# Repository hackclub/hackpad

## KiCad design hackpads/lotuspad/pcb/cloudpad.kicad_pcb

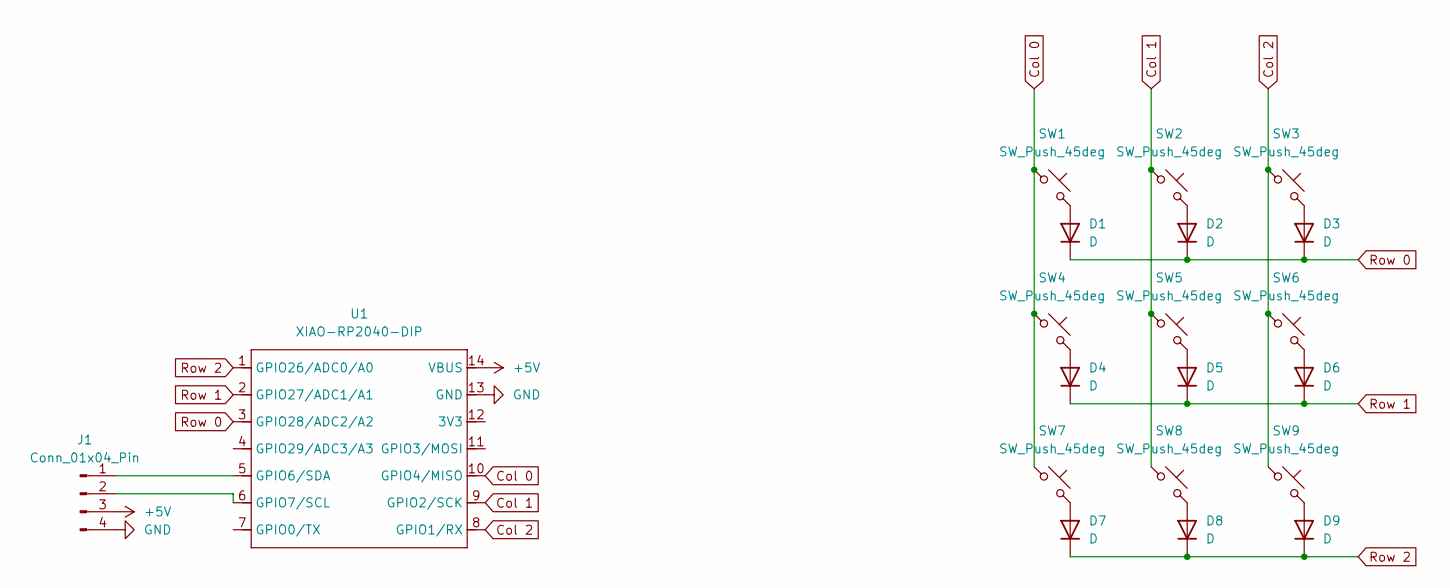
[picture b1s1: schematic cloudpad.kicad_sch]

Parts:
D1, D2, D3, D4, D5, D6, D7, D8, D9: D; Diode_DO-35
J1: Conn_01x04_Pin; MODULE_DM-OLED096-636
SW1, SW2, SW3, SW4, SW5, SW6, SW7, SW8, SW9: SW_Push_45deg; SW_Cherry_MX_1.00u_PCB
U1: XIAO-RP2040-DIP

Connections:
+5V: J1.3, U1.14 (VBUS)
Col 0: SW1.1, SW4.1, SW7.1, U1.10 (GPIO4/MISO)
Col 1: SW2.1, SW5.1, SW8.1, U1.9 (GPIO2/SCK)
Col 2: SW3.1, SW6.1, SW9.1, U1.8 (GPIO1/RX)
GND: J1.4, U1.13 (GND)
unnamed: D1.2 (A), SW1.2
unnamed: D2.2 (A), SW2.2
unnamed: D3.2 (A), SW3.2
unnamed: D4.2 (A), SW4.2
unnamed: D5.2 (A), SW5.2
unnamed: D6.2 (A), SW6.2
unnamed: D7.2 (A), SW7.2
unnamed: D8.2 (A), SW8.2
unnamed: D9.2 (A), SW9.2
unnamed: J1.1, U1.5 (GPIO6/SDA)
unnamed: J1.2, U1.6 (GPIO7/SCL)
Row 0: D1.1 (K), D2.1 (K), D3.1 (K), U1.3 (GPIO28/ADC2/A2)
Row 1: D4.1 (K), D5.1 (K), D6.1 (K), U1.2 (GPIO27/ADC1/A1)
Row 2: D7.1 (K), D8.1 (K), D9.1 (K), U1.1 (GPIO26/ADC0/A0)

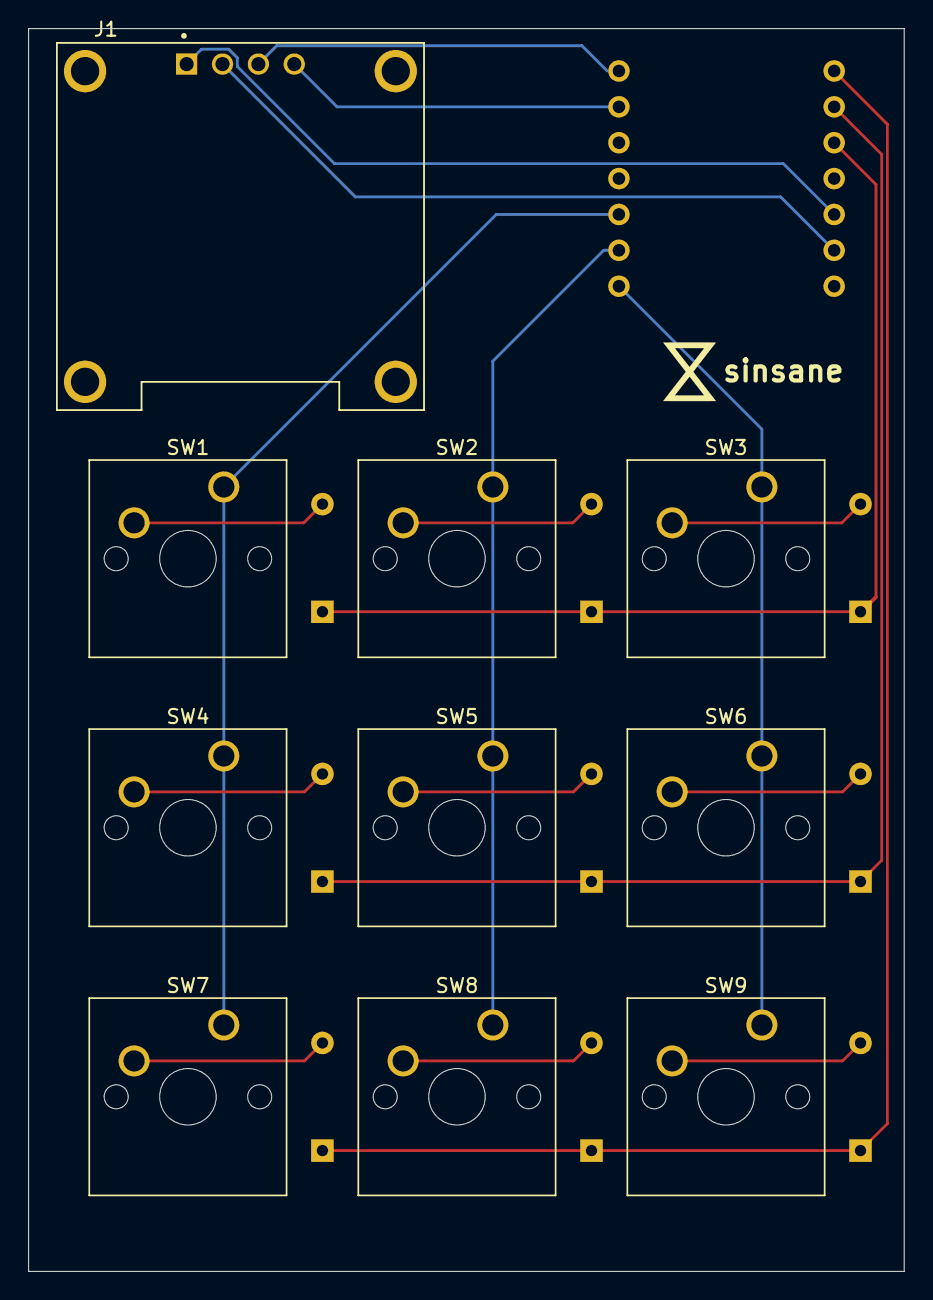
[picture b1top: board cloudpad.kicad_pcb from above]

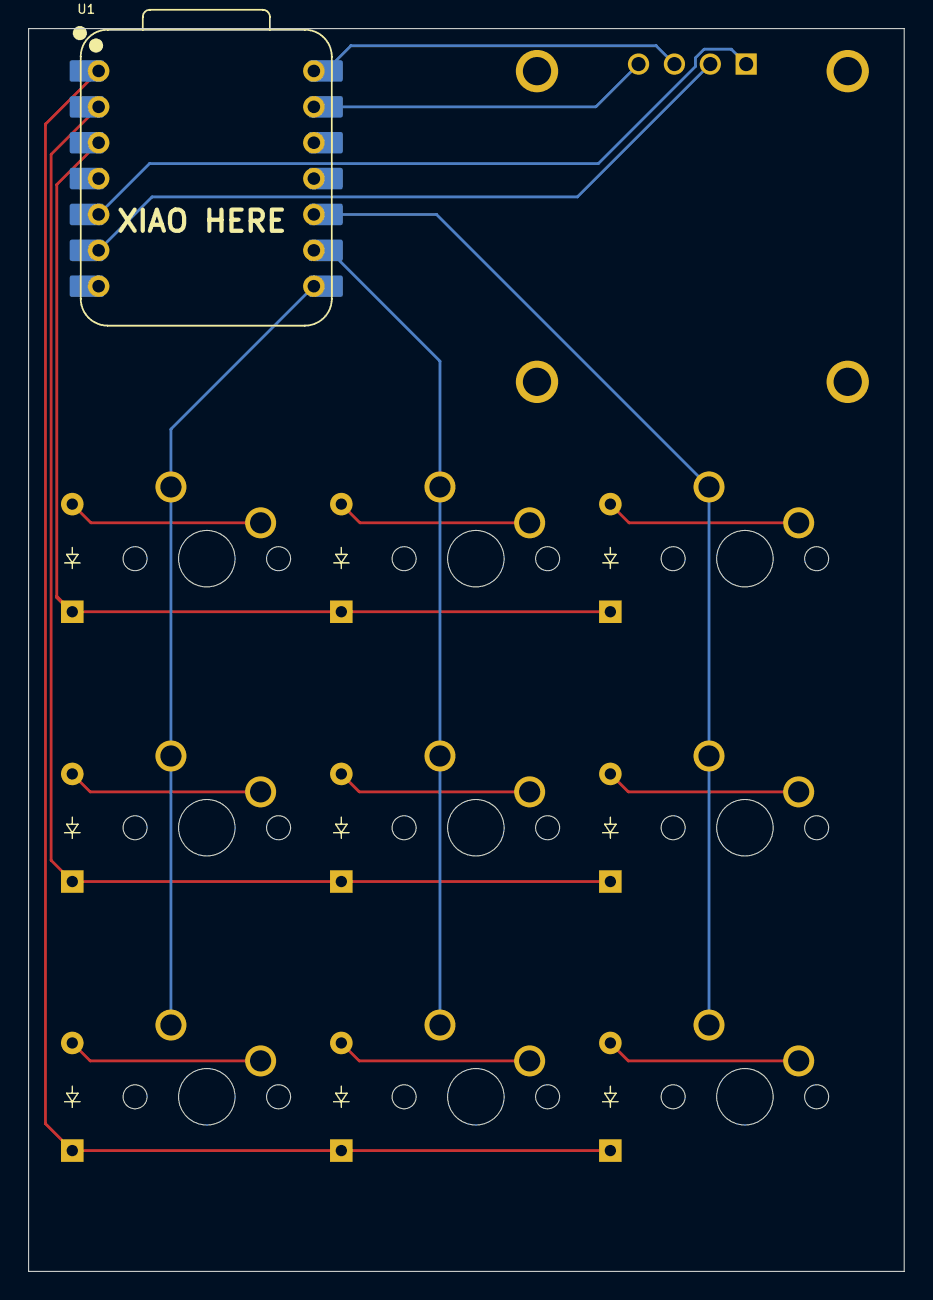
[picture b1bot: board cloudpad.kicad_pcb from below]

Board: 2 copper layers, 62.0 x 88.0 mm, 20 parts (10 on the bottom side), 19 nets.

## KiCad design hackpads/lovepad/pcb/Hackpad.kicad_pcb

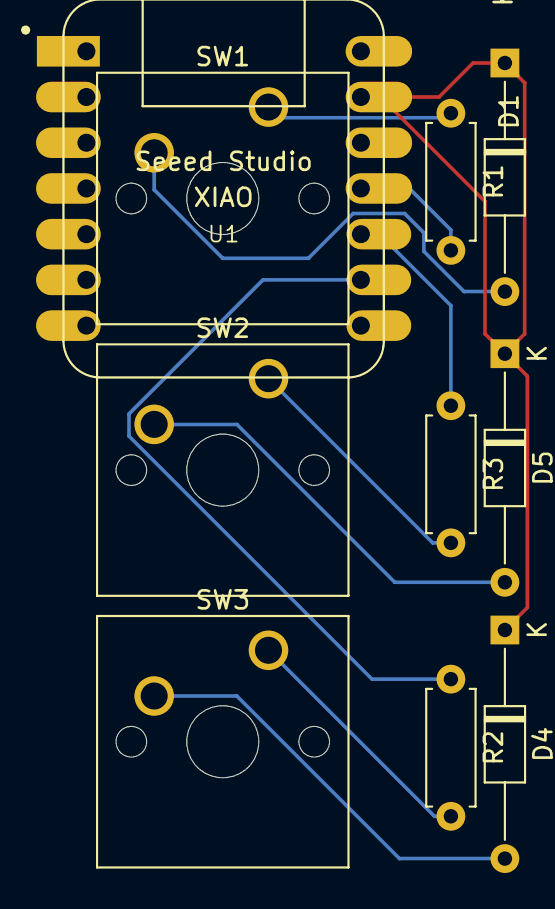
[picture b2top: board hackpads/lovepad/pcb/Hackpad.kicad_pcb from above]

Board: 2 copper layers, 10 parts (0 on the bottom side), 10 nets.

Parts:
D1, D4, D5: LED; D_DO-35_SOD27_P12.70mm_Horizontal
R1, R2, R3: R; R_Axial_DIN0207_L6.3mm_D2.5mm_P7.62mm_Horizontal
SW1, SW2, SW3: SW_Push; SW_Cherry_MX_1.00u_PCB
U1: Seeed Studio XIAO SAMD21; XIAO-Generic-Hybrid-14P-2.54-21X17.8MM

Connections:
GND: D1.1 (K), D4.1 (K), D5.1 (K), U1.13 (GND)
unnamed: D1.2 (A), SW1.2
unnamed: D4.2 (A), SW3.2
unnamed: D5.2 (A), SW2.2
unnamed: R1.1, SW1.1
unnamed: R2.2, SW3.1
unnamed: R3.2, SW2.1
unnamed: R3.1, U1.10 (PA5_A9_D9_MISO)
unnamed: R1.2, U1.11 (PA6_A10_D10_MOSI)
unnamed: R2.1, U1.9 (PA7_A8_D8_SCK)

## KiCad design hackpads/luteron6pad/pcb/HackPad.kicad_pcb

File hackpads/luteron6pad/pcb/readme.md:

The zip file is the gerber files for production.
The rest are KiCad project files.

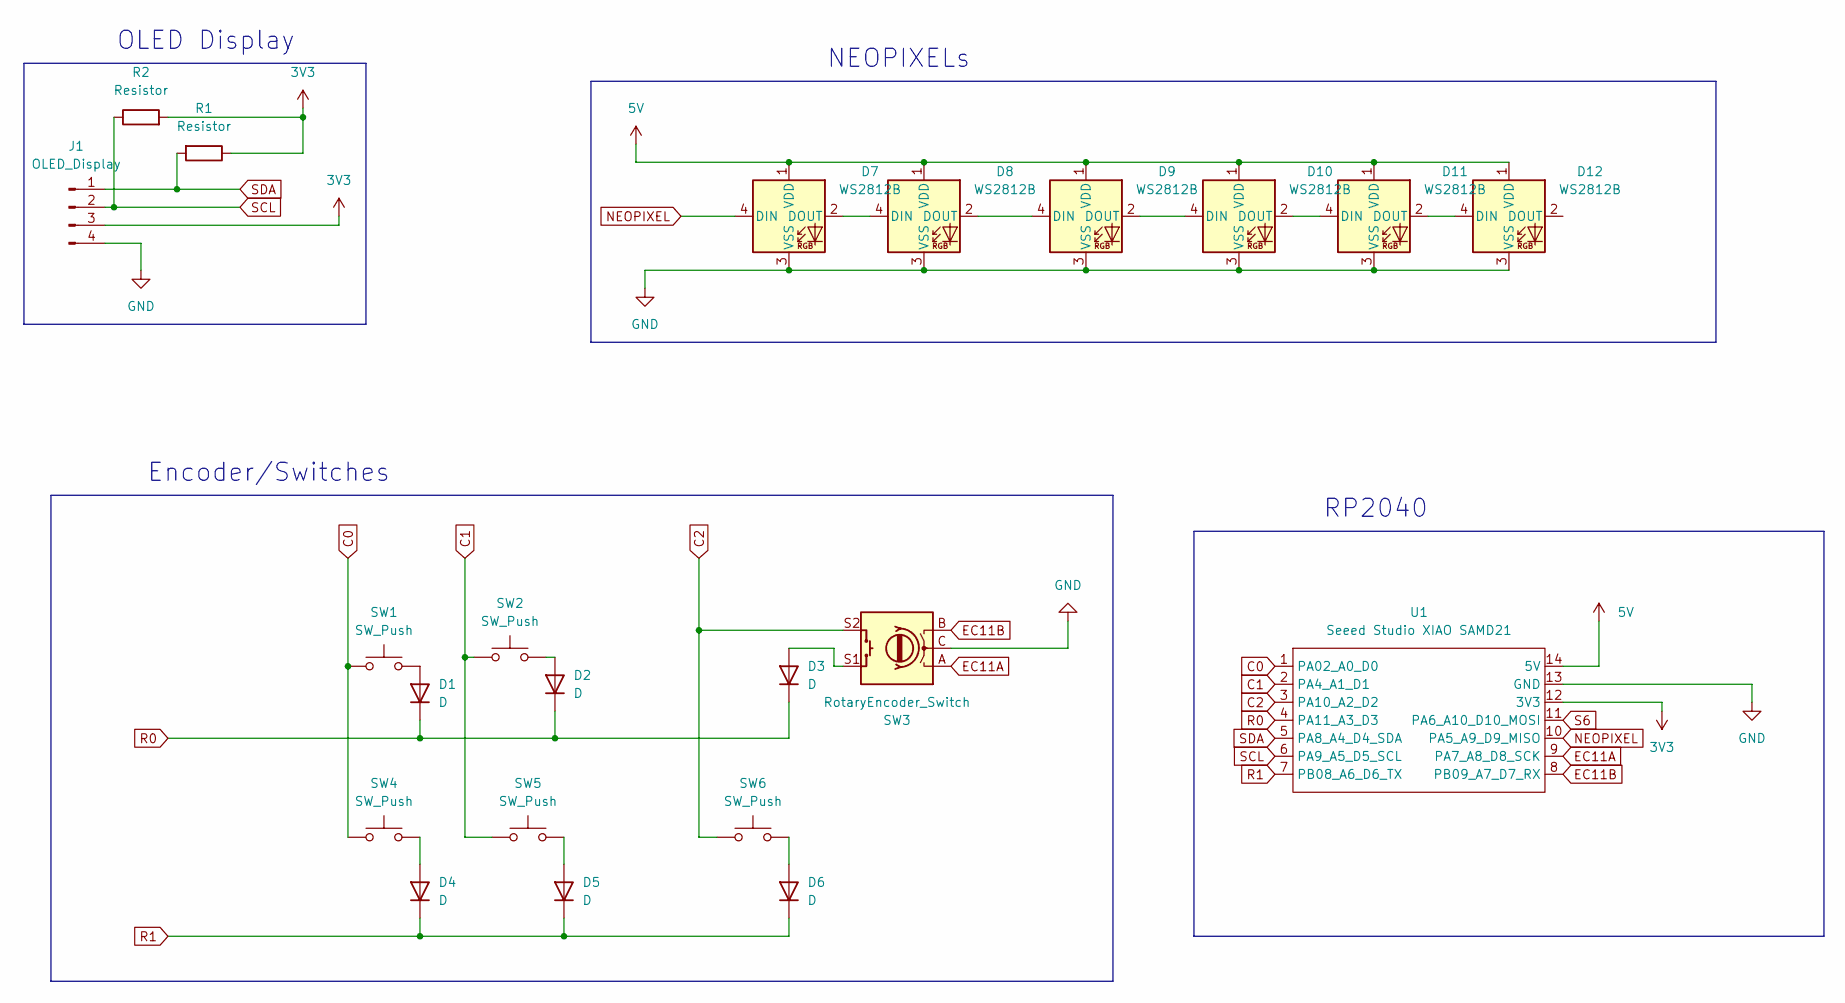
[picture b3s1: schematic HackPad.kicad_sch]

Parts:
D1, D2, D3, D4, D5, D6: D; D_DO-35_SOD27_P7.62mm_Horizontal
D7, D8, D9, D10, D11, D12: WS2812B; LED_WS2812B_PLCC4_5.0x5.0mm_P3.2mm
J1: OLED_Display; OLED_128x64
R1, R2: Resistor; R_0402_1005Metric
SW1, SW2, SW4, SW5, SW6: SW_Push; MX_PCB_1.00u
SW3: RotaryEncoder_Switch; Encoder_EC11_MX
U1: Seeed Studio XIAO SAMD21; Seeed_XIAO_RP2040

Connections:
3V3: J1.3, R1.1, R2.2, U1.12 (3V3)
5V: D7.1 (VDD), D8.1 (VDD), D9.1 (VDD), D10.1 (VDD), D11.1 (VDD), D12.1 (VDD), U1.14 (5V)
C0: SW1.1, SW4.1, U1.1 (PA02_A0_D0)
C1: SW2.1, SW5.1, U1.2 (PA4_A1_D1)
C2: SW3.S2, SW6.1, U1.3 (PA10_A2_D2)
EC11A: SW3.A, U1.9 (PA7_A8_D8_SCK)
EC11B: SW3.B, U1.8 (PB09_A7_D7_RX)
GND: D7.3 (VSS), D8.3 (VSS), D9.3 (VSS), D10.3 (VSS), D11.3 (VSS), D12.3 (VSS), J1.4, SW3.C, U1.13 (GND)
NEOPIXEL: D7.4 (DIN), U1.10 (PA5_A9_D9_MISO)
unnamed: D1.2 (A), SW1.2
unnamed: D2.2 (A), SW2.2
unnamed: D3.2 (A), SW3.S1
unnamed: D4.2 (A), SW4.2
unnamed: D5.2 (A), SW5.2
unnamed: D6.2 (A), SW6.2
unnamed: D7.2 (DOUT), D8.4 (DIN)
unnamed: D8.2 (DOUT), D9.4 (DIN)
unnamed: D9.2 (DOUT), D10.4 (DIN)
unnamed: D10.2 (DOUT), D11.4 (DIN)
unnamed: D11.2 (DOUT), D12.4 (DIN)
R0: D1.1 (K), D2.1 (K), D3.1 (K), U1.4 (PA11_A3_D3)
R1: D4.1 (K), D5.1 (K), D6.1 (K), U1.7 (PB08_A6_D6_TX)
S6: U1.11 (PA6_A10_D10_MOSI)
SCL: J1.2, R2.1, U1.6 (PA9_A5_D5_SCL)
SDA: J1.1, R1.2, U1.5 (PA8_A4_D4_SDA)

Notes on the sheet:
RP2040
OLED Display
NEOPIXELs
Encoder/Switches

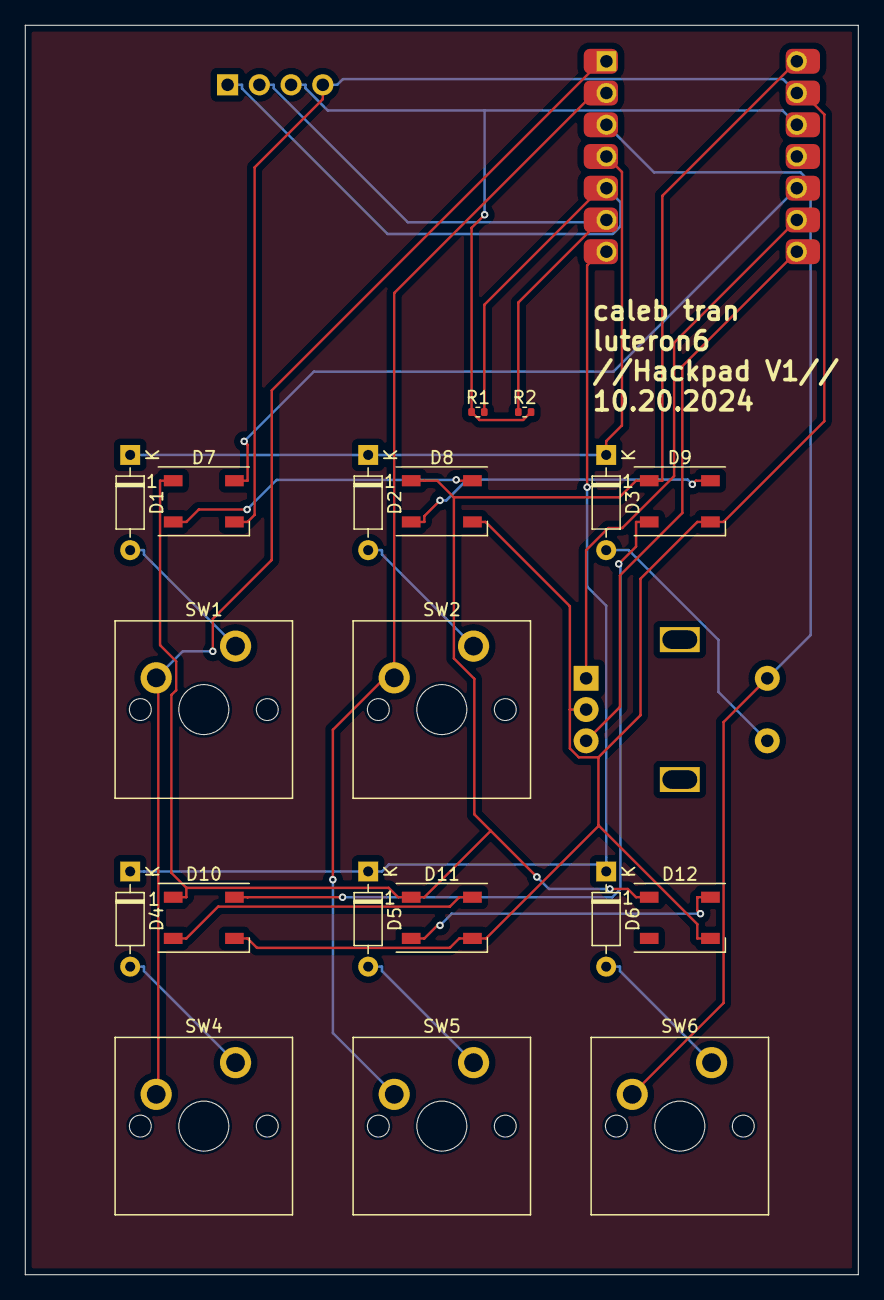
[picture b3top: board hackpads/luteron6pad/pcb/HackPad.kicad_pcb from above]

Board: 2 copper layers, 66.7 x 100.0 mm, 22 parts (0 on the bottom side), 24 nets.

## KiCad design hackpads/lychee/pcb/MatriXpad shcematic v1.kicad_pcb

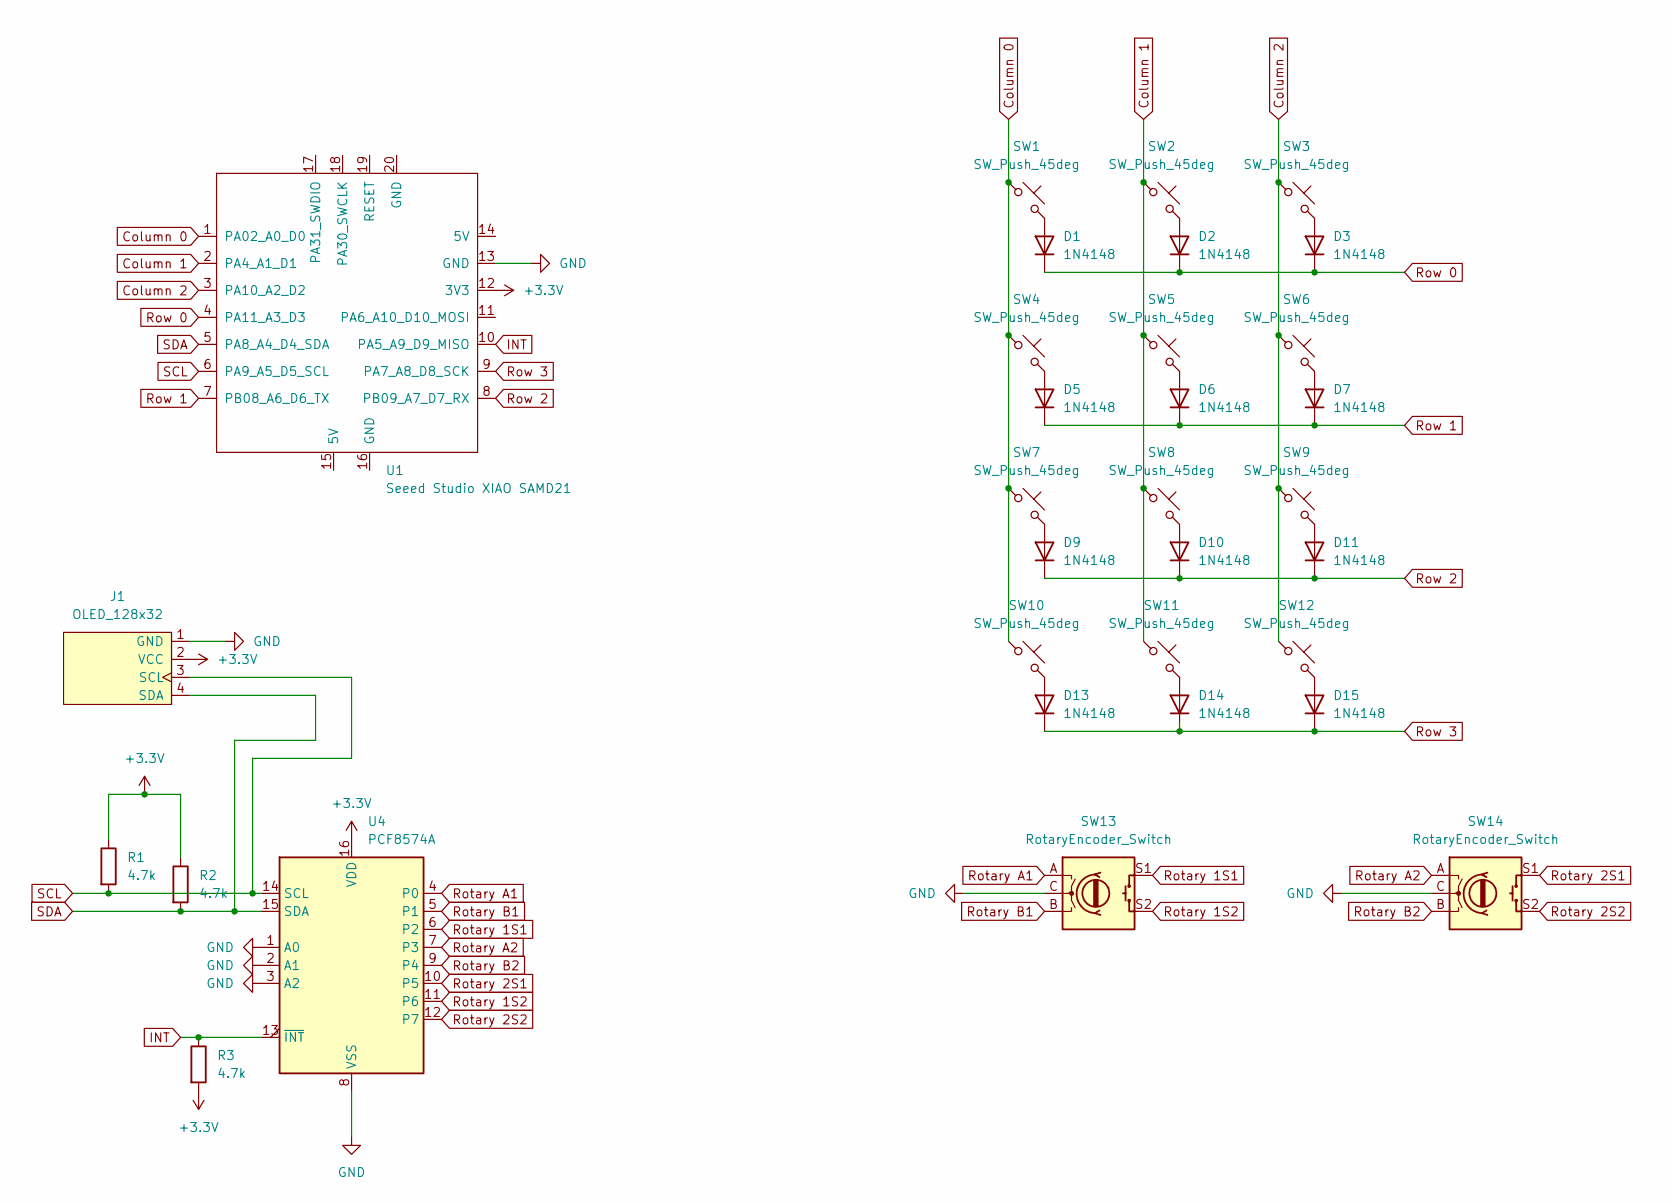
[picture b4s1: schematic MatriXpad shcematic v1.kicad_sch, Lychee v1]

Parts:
D1, D2, D3, D5, D6, D7, D9, D10, D11, D13, D14, D15: 1N4148; D_DO-35_SOD27_P7.62mm_Horizontal
J1: OLED_128x32; OLED128x32
R1, R2, R3: 4.7k; RESAD700W45L350D185
SW1, SW2, SW3, SW4, SW5, SW6, SW7, SW8, SW9, SW10, SW11, SW12: SW_Push_45deg; SW_Cherry_MX_1.00u_PCB
SW13, SW14: RotaryEncoder_Switch; RotaryEncoder_Alps_EC11E-Switch_Vertical_H20mm
U1: Seeed Studio XIAO SAMD21; Seeed_XIAO_RP2040
U4: PCF8574A; N16

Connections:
+3.3V: J1.2 (VCC), R1.1, R2.1, R3.2, U1.12 (3V3), U4.16 (VDD)
Column 0: SW1.1, SW4.1, SW7.1, SW10.1, U1.1 (PA02_A0_D0)
Column 1: SW2.1, SW5.1, SW8.1, SW11.1, U1.2 (PA4_A1_D1)
Column 2: SW3.1, SW6.1, SW9.1, SW12.1, U1.3 (PA10_A2_D2)
GND: J1.1 (GND), SW13.C, SW14.C, U1.13 (GND), U4.1 (A0), U4.2 (A1), U4.3 (A2), U4.8 (VSS)
INT: R3.1, U1.10 (PA5_A9_D9_MISO), U4.13 (~INT)
unnamed: D1.2 (A), SW1.2
unnamed: D2.2 (A), SW2.2
unnamed: D3.2 (A), SW3.2
unnamed: D5.2 (A), SW4.2
unnamed: D6.2 (A), SW5.2
unnamed: D7.2 (A), SW6.2
unnamed: D9.2 (A), SW7.2
unnamed: D10.2 (A), SW8.2
unnamed: D11.2 (A), SW9.2
unnamed: D13.2 (A), SW10.2
unnamed: D14.2 (A), SW11.2
unnamed: D15.2 (A), SW12.2
Rotary 1S1: SW13.S1, U4.6 (P2)
Rotary 1S2: SW13.S2, U4.11 (P6)
Rotary 2S1: SW14.S1, U4.10 (P5)
Rotary 2S2: SW14.S2, U4.12 (P7)
Rotary A1: SW13.A, U4.4 (P0)
Rotary A2: SW14.A, U4.7 (P3)
Rotary B1: SW13.B, U4.5 (P1)
Rotary B2: SW14.B, U4.9 (P4)
Row 0: D1.1 (K), D2.1 (K), D3.1 (K), U1.4 (PA11_A3_D3)
Row 1: D5.1 (K), D6.1 (K), D7.1 (K), U1.7 (PB08_A6_D6_TX)
Row 2: D9.1 (K), D10.1 (K), D11.1 (K), U1.8 (PB09_A7_D7_RX)
Row 3: D13.1 (K), D14.1 (K), D15.1 (K), U1.9 (PA7_A8_D8_SCK)
SCL: J1.3 (SCL), R1.2, U1.6 (PA9_A5_D5_SCL), U4.14 (SCL)
SDA: J1.4 (SDA), R2.2, U1.5 (PA8_A4_D4_SDA), U4.15 (SDA)

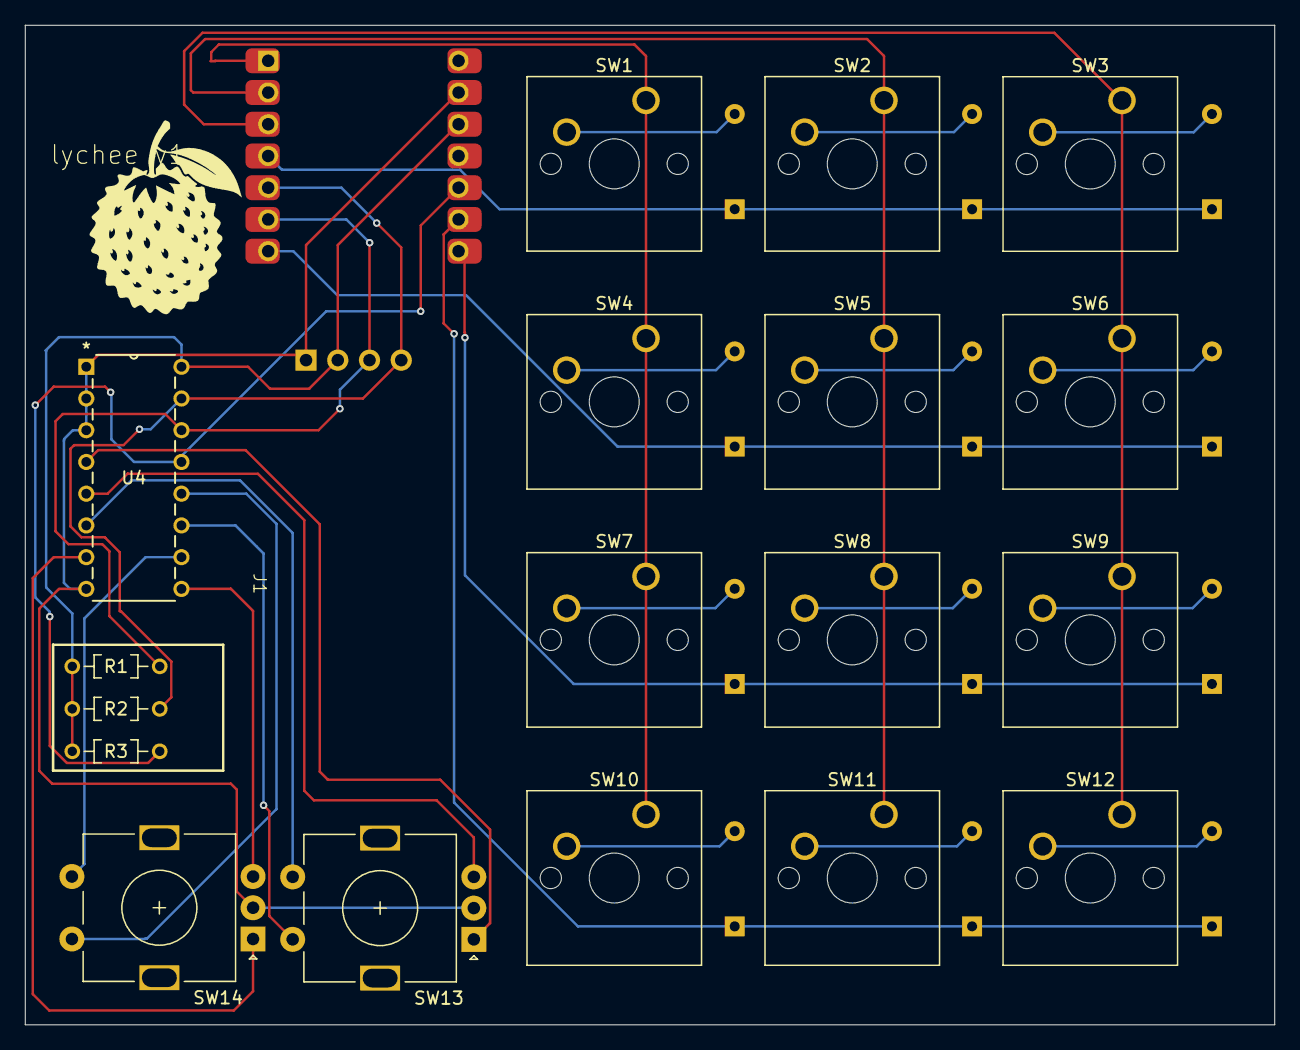
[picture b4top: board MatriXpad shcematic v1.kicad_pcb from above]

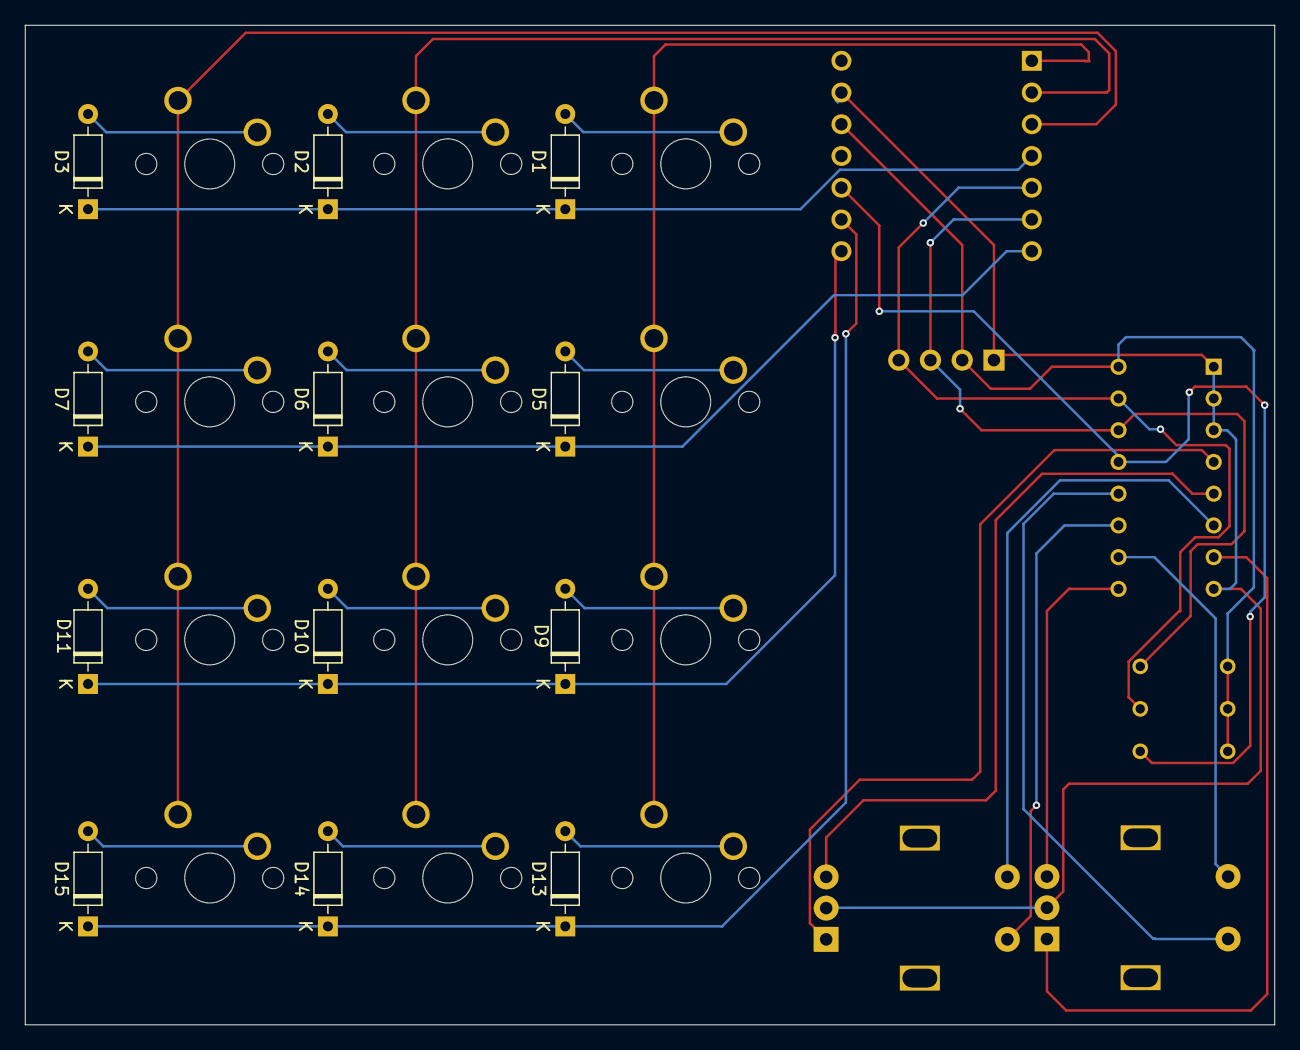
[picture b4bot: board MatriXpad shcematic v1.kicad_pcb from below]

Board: 2 copper layers, 100.0 x 80.0 mm, 32 parts (12 on the bottom side), 32 nets.

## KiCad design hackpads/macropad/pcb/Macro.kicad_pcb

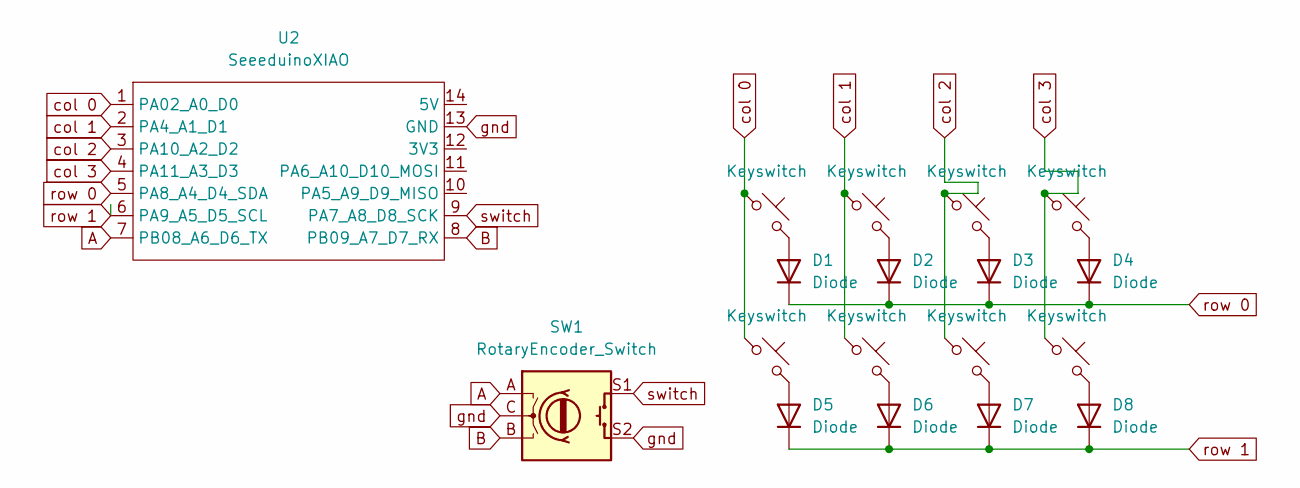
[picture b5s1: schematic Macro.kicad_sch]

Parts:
D1, D2, D3, D4, D5, D6, D7, D8: Diode; Diode_DO-35
S1, S2, S3, S4, S5, S6, S7, S8: Keyswitch; MX_PCB_1.00u
SW1: RotaryEncoder_Switch; Encoder_EC11_MX
U2: SeeeduinoXIAO; Seeed_XIAO_RP2040

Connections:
A: SW1.A, U2.7 (PB08_A6_D6_TX)
B: SW1.B, U2.8 (PB09_A7_D7_RX)
unnamed: D1.2 (A), S1.2
unnamed: D2.2 (A), S2.2
unnamed: D3.2 (A), S3.2
unnamed: D4.2 (A), S4.2
unnamed: D5.2 (A), S5.2
unnamed: D6.2 (A), S6.2
unnamed: D7.2 (A), S7.2
unnamed: D8.2 (A), S8.2
col 0: S1.1, S5.1, U2.1 (PA02_A0_D0)
col 1: S2.1, S6.1, U2.2 (PA4_A1_D1)
col 2: S3.1, S7.1, U2.3 (PA10_A2_D2)
col 3: S4.1, S8.1, U2.4 (PA11_A3_D3)
gnd: SW1.C, SW1.S2, U2.13 (GND)
row 0: D1.1 (K), D2.1 (K), D3.1 (K), D4.1 (K), U2.5 (PA8_A4_D4_SDA)
row 1: D5.1 (K), D6.1 (K), D7.1 (K), D8.1 (K), U2.6 (PA9_A5_D5_SCL)
switch: SW1.S1, U2.9 (PA7_A8_D8_SCK)

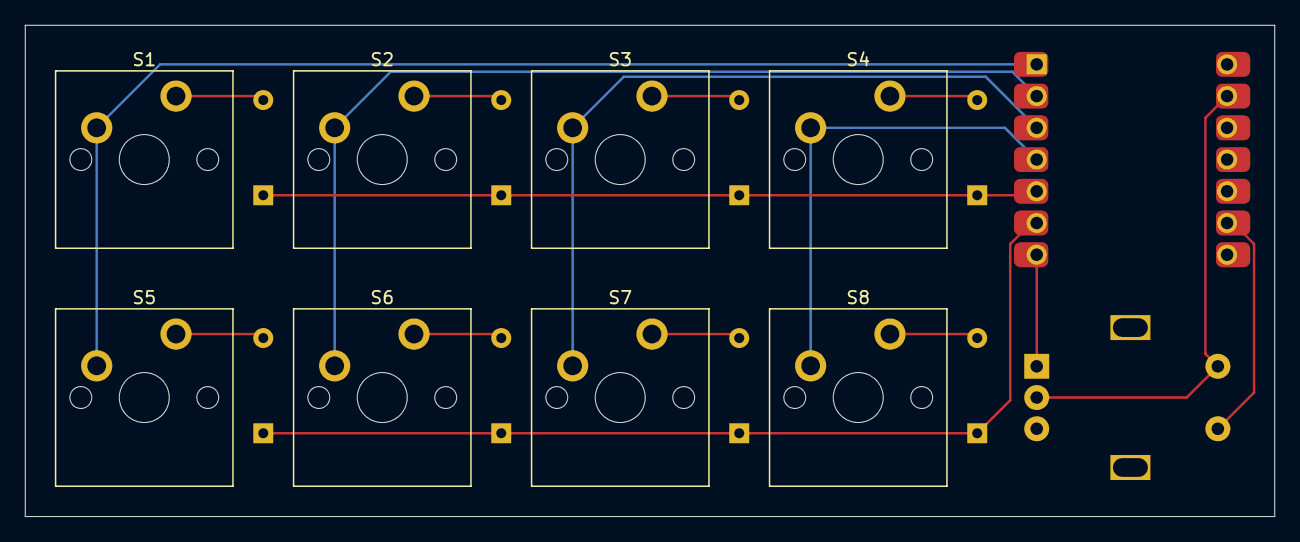
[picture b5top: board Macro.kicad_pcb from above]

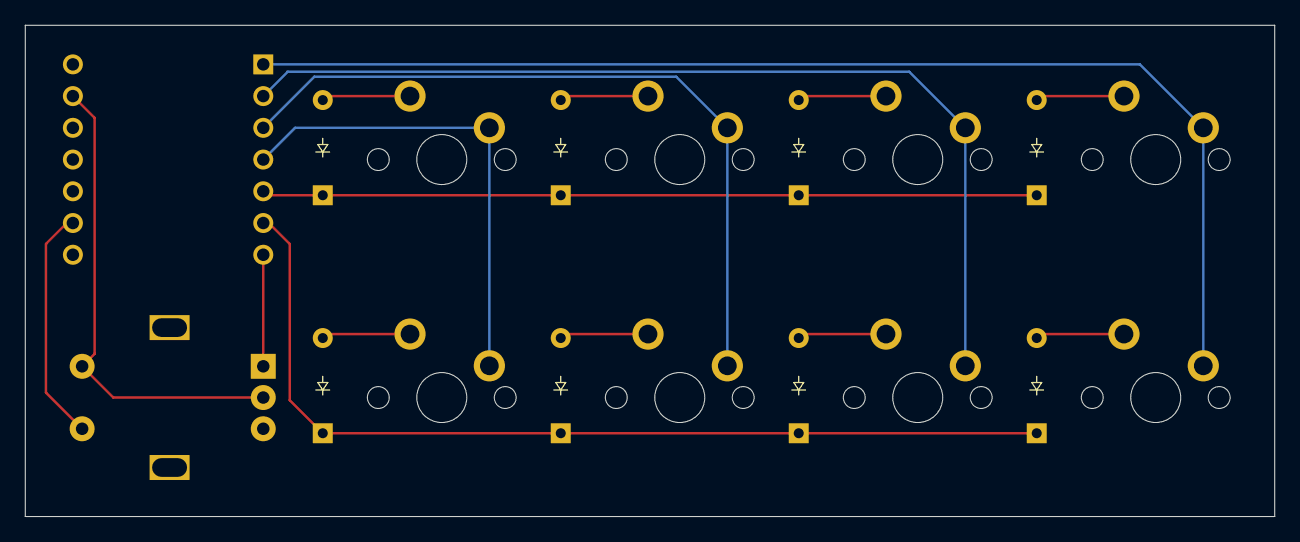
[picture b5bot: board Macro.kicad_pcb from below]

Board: 2 copper layers, 100.0 x 39.3 mm, 18 parts (8 on the bottom side), 18 nets.

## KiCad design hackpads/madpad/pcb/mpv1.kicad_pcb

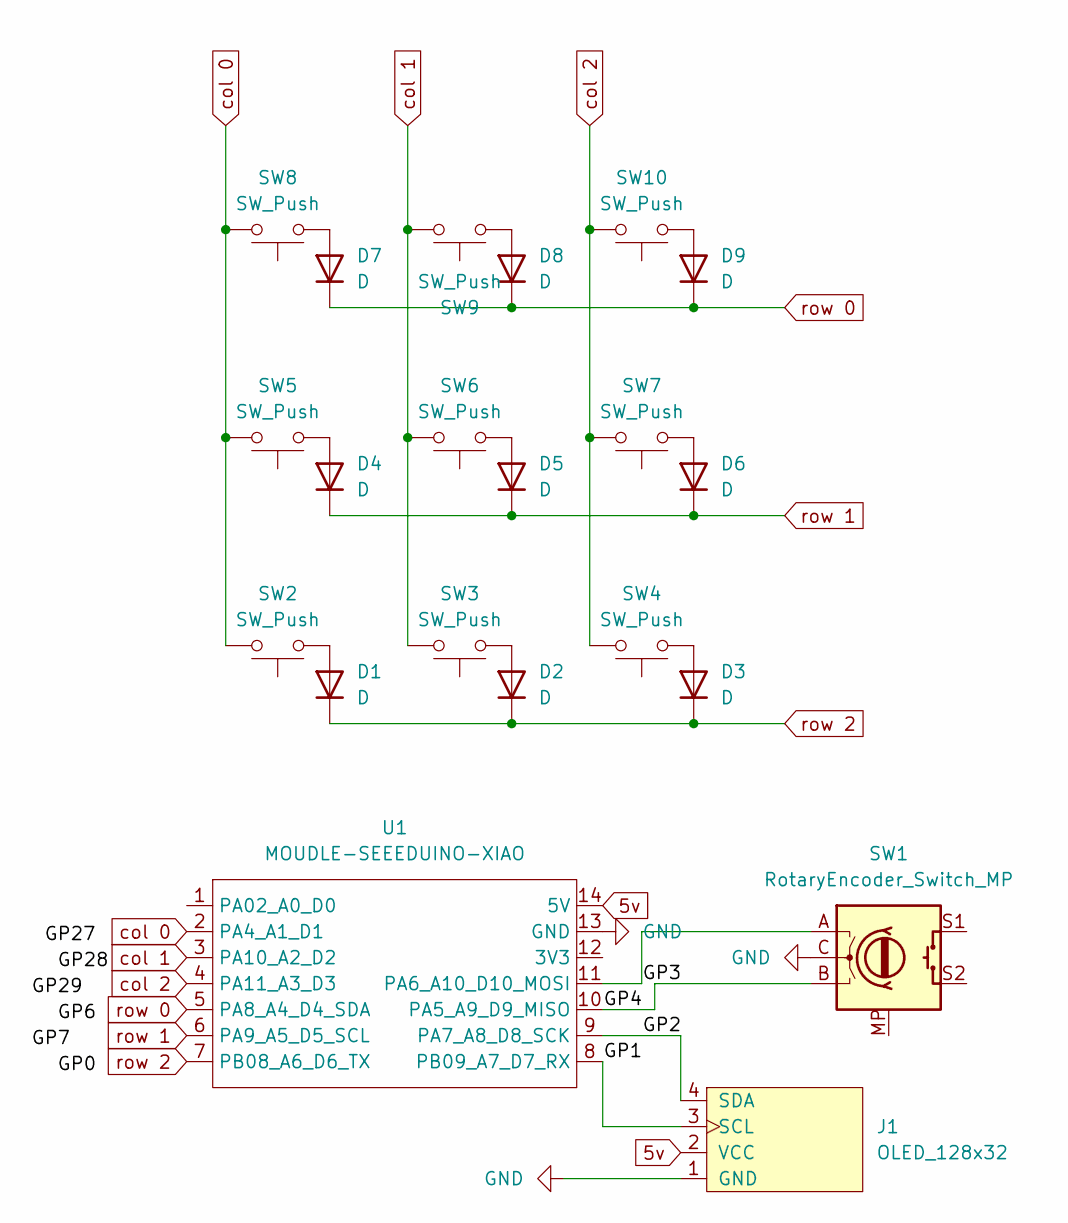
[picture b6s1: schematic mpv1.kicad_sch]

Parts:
D1, D2, D3, D4, D5, D6, D7, D8, D9: D; Diode_DO-35
J1: OLED_128x32; SSD1306-0.91-OLED-4pin-128x32
SW1: RotaryEncoder_Switch_MP; Encoder_EC11_MX
SW2, SW3, SW4, SW5, SW6, SW7, SW8, SW9, SW10: SW_Push; SW_Cherry_MX_1.00u_PCB
U1: MOUDLE-SEEEDUINO-XIAO; XIAO-Generic-Hybrid-14P-2.54-21X17.8MM

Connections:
5v: J1.2 (VCC), U1.14 (5V); also elsewhere on the board
GND: J1.1 (GND), SW1.C, U1.13 (GND); also elsewhere on the board
unnamed: D1.2 (A), SW2.1
unnamed: D2.2 (A), SW3.1
unnamed: D3.2 (A), SW4.1
unnamed: D4.2 (A), SW5.1
unnamed: D5.2 (A), SW6.1
unnamed: D6.2 (A), SW7.1
unnamed: D7.2 (A), SW8.1
unnamed: D8.2 (A), SW9.1
unnamed: D9.2 (A), SW10.1
unnamed 11: J1.3 (SCL), U1.8 (PB09_A7_D7_RX); also elsewhere on the board
unnamed 12: J1.4 (SDA), U1.9 (PA7_A8_D8_SCK); also elsewhere on the board
unnamed: SW1.B, U1.10 (PA5_A9_D9_MISO)
unnamed: SW1.A, U1.11 (PA6_A10_D10_MOSI)
col 0: SW2.2, SW5.2, SW8.2, U1.2 (PA4_A1_D1)
col 1: SW3.2, SW6.2, SW9.2, U1.3 (PA10_A2_D2)
col 2: SW4.2, SW7.2, SW10.2, U1.4 (PA11_A3_D3)
row 0: D7.1 (K), D8.1 (K), D9.1 (K), U1.5 (PA8_A4_D4_SDA)
row 1: D4.1 (K), D5.1 (K), D6.1 (K), U1.6 (PA9_A5_D5_SCL)
row 2: D1.1 (K), D2.1 (K), D3.1 (K), U1.7 (PB08_A6_D6_TX)

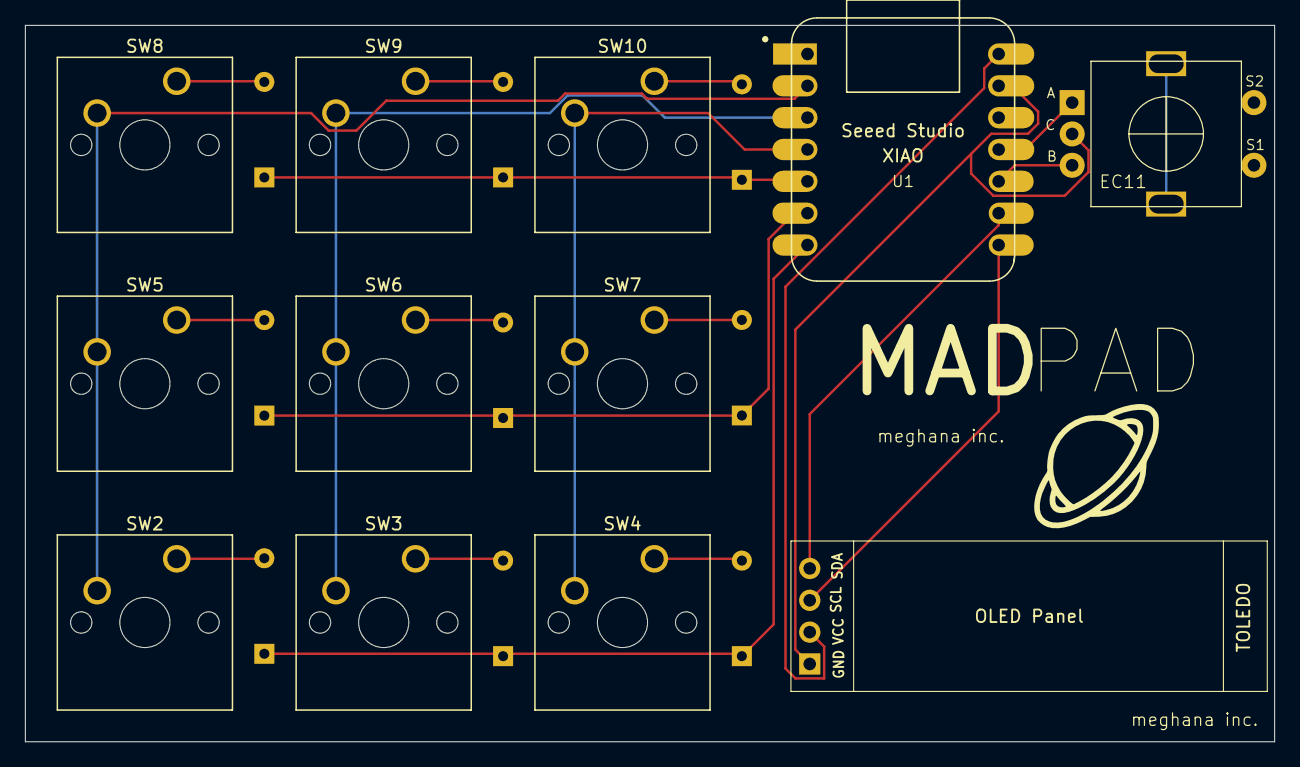
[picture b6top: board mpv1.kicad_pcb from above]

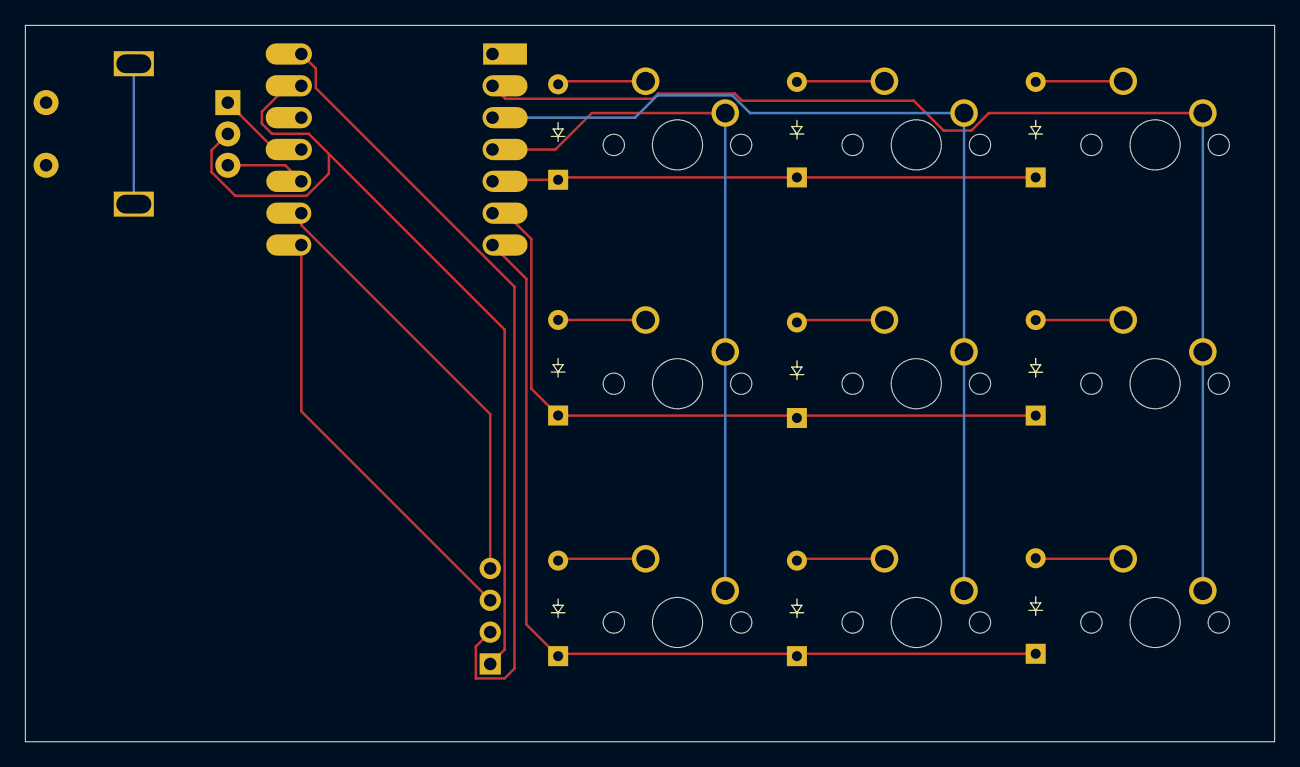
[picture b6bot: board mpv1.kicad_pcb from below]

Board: 2 copper layers, 99.7 x 57.2 mm, 21 parts (9 on the bottom side), 21 nets.

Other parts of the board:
TOLEDO: OLED_128x32; SSD1306-0.91-OLED-4pin-128x32

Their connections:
5v: TOLEDO.2 (VCC); also elsewhere on the board
GND: TOLEDO.1 (GND); also elsewhere on the board
unnamed 11: TOLEDO.3 (SCL); also elsewhere on the board
unnamed 12: TOLEDO.4 (SDA); also elsewhere on the board
